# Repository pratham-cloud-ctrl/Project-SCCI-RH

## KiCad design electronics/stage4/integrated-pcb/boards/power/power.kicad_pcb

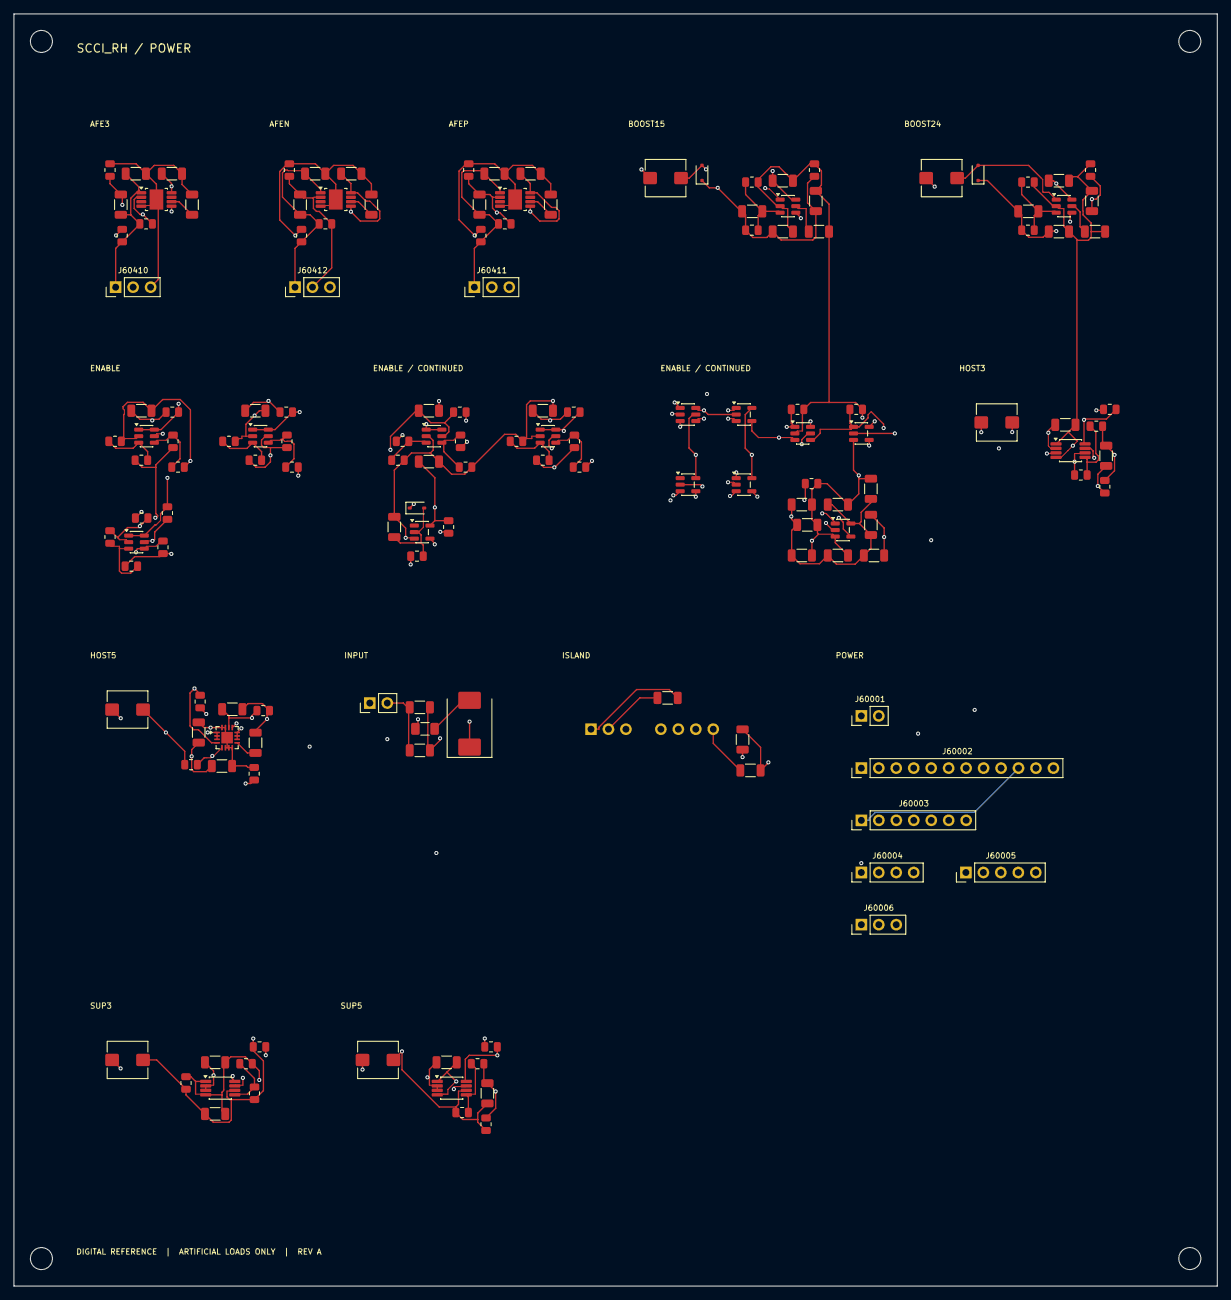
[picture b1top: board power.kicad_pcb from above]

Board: 4 copper layers, 175.0 x 185.0 mm, 160 parts (0 on the bottom side), 70 nets.

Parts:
C60001: 100u 16V LOW ESR; C_1206_3216Metric
C60002, C61102: 100n X7R 25V; C_1206_3216Metric
C60200, C60201, C60202, C60203, C60204, C60240, C60241, C60242, C60243, C60244, C60245, C60246, C60247: 100n X7R 16V; C_1206_3216Metric
C60230: 47n X7R 10%; C_1206_3216Metric
C60400, C61001, C61011, C61021, C61101: 22u X7R 16V; C_1206_3216Metric
C60401, C60402, C64100, C64110, C64120: 10u X7R 50V; C_1206_3216Metric
C61000, C61010, C61020, C61100, C63000, C63010: 10u X7R 25V; C_1206_3216Metric
C61103: 3.3n C0G 50V; C_1206_3216Metric
C63001, C63002, C63011, C63012: 22u X7R 50V; C_1206_3216Metric
C63003, C63013: 1u X7R 10V; C_1206_3216Metric
C63004, C63014: 4.7p C0G 50V; C_1206_3216Metric
C64101, C64111, C64121: 10u X7R 16V; C_1206_3216Metric
C64102, C64103, C64112, C64113, C64122, C64123: 10n C0G 50V; C_1206_3216Metric
D60001: SS34-E3/57T; D_SMC
D60230: BAT54WS-7-F; D_SOD-323
D60300, D60301: PMEG6010CEJ; D_SOD-323F
F60001: 2A FUSE 1206; Fuse_1206_3216Metric
H1, H2, H3, H4: MountingHole_3.2mm_M3
J60001: AT31004 PROTECTED 2S PACK / 6.4 TO 8.4V; PinHeader_1x02_P2.54mm_Vertical
J60002: POWER REQUEST / STATUS; PinHeader_1x12_P2.54mm_Vertical
J60003: HOST AND SUPERVISOR RAILS; PinHeader_1x07_P2.54mm_Vertical
J60004: FLOATING RECORDING RAILS; PinHeader_1x04_P2.54mm_Vertical
J60005: CONVERTER TEST POINTS; PinHeader_1x05_P2.54mm_Vertical
J60006: EXISTING MONITOR REFERENCES; PinHeader_1x03_P2.54mm_Vertical
J60410, J60411, J60412: QUIESCENT TRIM / TEST ONLY; PinHeader_1x03_P2.54mm_Vertical
L60100, L60101, L60102, L60110: 2.2uH SRP5030T-2R2M; L_Bourns_SRP5030T
L60300, L60301: 4.7uH SRP5030T-4R7M; L_Bourns_SRP5030T
R60230: 100k 1%; R_0805_2012Metric
R60231: 100R; R_0805_2012Metric
R60240, R60241, R60242, R62004, R62014, R62024, R62034, R62044: 10k; R_0805_2012Metric
R61000, R61020: 31250R 0.1%; R_0805_2012Metric
R61001, R61011, R61021: 10000R 0.1%; R_0805_2012Metric
R61002, R61012, R61022, R61102, R63002, R63012: 100k; R_0805_2012Metric
R61003, R61013, R61023, R61103, R64102, R64112, R64122: 47k; R_0805_2012Metric
R61010: 52500R 0.1%; R_0805_2012Metric
R61100: 52.5k 0.1%; R_0805_2012Metric
R61101, R62001, R62003, R62011, R62013, R62021, R62023, R62031, R62033, R62041, R62043, R64101, R64111, R64121: 10k 0.1%; R_0805_2012Metric
R62000: 155000R 0.1%; R_0805_2012Metric
R62002: 205000R 0.1%; R_0805_2012Metric
R62010: 67500R 0.1%; R_0805_2012Metric
R62012: 77500R 0.1%; R_0805_2012Metric
R62020: 108750R 0.1%; R_0805_2012Metric
R62022: 121250R 0.1%; R_0805_2012Metric
R62030: 89500R 0.1%; R_0805_2012Metric
R62032: 95500R 0.1%; R_0805_2012Metric
R62040: 39500R 0.1%; R_0805_2012Metric
R62042: 43000R 0.1%; R_0805_2012Metric
R63000: 418750R 0.1%; R_0805_2012Metric
R63001, R63011: 50k 0.1%; R_0805_2012Metric
R63010: 700000R 0.1%; R_0805_2012Metric
R64100: 19113.924R 0.1%; R_0805_2012Metric
R64110: 34725.738R 0.1%; R_0805_2012Metric
R64120: 33367.347R 0.1%; R_0805_2012Metric
SW60001: MASTER SPST / OFFBOARD; PinHeader_1x02_P2.54mm_Vertical
U60100, U60101, U60102: TPS62160DGKR; VSSOP-8_3x3mm_P0.65mm
U60110: TPS62130ARGTR; VQFN-16-1EP_3x3mm_P0.5mm_EP1.68x1.68mm
U60200, U60201, U60202, U60203, U60204: TPS3700DDCR; SOT-23-6
U60230: SN74LVC1G17DBVR; SOT-23-5
U60231, U60233: SN74LVC1G11DBVR; SOT-23-6
U60232, U60234, U60236, U60237: SN74LVC1G08DBVR; SOT-23-5
U60235: SN74LVC1G07DBVR; SOT-23-5
U60300, U60301: LT8330ES6#TRPBF; TSOT-23-6
U60400: TMR3-0522; TRACO_TMR3_SIP8_21.8x9.1_P2.54
U60410, U60411: TPS7A4901DGNR; Texas_DGN0008D_VSSOP-8-1EP_3x3mm_P0.65mm_EP2x2.94mm_Mask1.5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
U60412: TPS7A3001DGNR; Texas_DGN0008D_VSSOP-8-1EP_3x3mm_P0.65mm_EP2x2.94mm_Mask1.5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

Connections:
SYS_3fdd5066__AFE_P5: C64111.1, C64113.1, J60004.2, J60411.1, R64110.1, R64112.1, U60411.1
SYS_4f66f129__MON_VREF: J60006.1, R62030.1, R62032.1
SYS_37cfe02a__MON_VMID: J60006.2, R62040.1, R62042.1
SYS_65aafbb6__AFE_3V3: C64101.1, C64103.1, J60004.1, J60410.1, R64100.1, R64102.1, U60410.1
SYS_66aba95b__SUP_5: C61011.1, J60003.2, L60101.2, R61010.1, R61013.1, R62020.1, R62022.1, U60101.6
SYS_15689dc4__VH_24: C63011.1, C63012.1, C63014.1, D60301.1, J60003.6, R63010.1, R63012.1
SYS_56562df4__GND: C60001.2, C60002.2, C60200.2, C60201.2, C60202.2, C60203.2, C60204.2, C60230.2, C60240.2, C60241.2, C60242.2, C60243.2, C60244.2, C60245.2, C60246.2, C60247.2, C60400.2, C61000.2, C61001.2, C61010.2, C61011.2, C61020.2, C61021.2, C61100.2, C61101.2, C61102.2, C61103.2, C63000.2, C63001.2, C63002.2, C63003.2, C63010.2, C63011.2, C63012.2, C63013.2, J60001.2, J60002.12, J60003.7, J60005.5, J60006.3, R60240.2, R60241.2, R60242.2, R61001.2, R61003.2, R61011.2, R61013.2, R61021.2, R61023.2, R61101.2, R61103.2, R62001.2, R62003.2, R62011.2, R62013.2, R62021.2, R62023.2, R62031.2, R62033.2, R62041.2, R62043.2, R63001.2, R63002.2, R63011.2, R63012.2, U60100.1, U60100.4, U60101.1, U60101.4, U60102.1, U60102.4, U60110.6, U60110.7, U60110.8, U60110.15, U60110.16, U60110.17, U60200.2, U60201.2, U60202.2, U60203.2, U60204.2, U60230.3, U60231.2, U60232.3, U60233.2, U60234.3, U60235.3, U60236.3, U60237.3, U60300.2, U60301.2, U60400.1
SYS_08572049__HOST_3V3: C61021.1, J60003.3, L60102.2, R61020.1, R61023.1, U60102.6
SYS_ab932142__SUP_3V3: C60200.1, C60201.1, C60202.1, C60203.1, C60204.1, C60240.1, C60241.1, C60242.1, C60243.1, C60244.1, C60245.1, C60246.1, C60247.1, C61001.1, J60002.10, J60003.1, L60100.2, R60230.1, R60231.2, R61000.1, R61002.1, R61003.1, R61012.1, R61022.1, R61102.1, R62004.1, R62010.1, R62012.1, R62014.1, R62024.1, R62034.1, R62044.1, U60100.6, U60200.5, U60201.5, U60202.5, U60203.5, U60204.5, U60230.5, U60231.5, U60232.5, U60233.5, U60234.5, U60235.5, U60236.5, U60237.5
SYS_ce166826__HOST_5: C60400.1, C61101.1, J60003.4, L60110.2, R61100.1, R61103.1, U60110.14, U60400.2
SYS_d73cd2ee__AFE_N5: C64121.1, C64123.1, J60004.3, J60412.1, R64120.1, R64122.1, U60412.1
SYS_ee59c76b__PWR_FAULT_N: J60002.11, U60235.4
SYS_f199d834__PACK_BUS: C60001.1, C60002.1, C61000.1, C61010.1, C61020.1, C61100.1, C61102.1, C63000.1, C63010.1, J60005.1, L60300.1, L60301.1, SW60001.2, U60100.2, U60100.3, U60101.2, U60101.3, U60102.2, U60110.10, U60110.11, U60110.12, U60300.6, U60301.6
SYS_fb2237f8__VA_15: C63001.1, C63002.1, C63004.1, D60300.1, J60003.5, R63000.1, R63002.1
SYS_fca1c340__AFEAGND: C60401.2, C60402.2, C64100.2, C64101.2, C64102.2, C64110.2, C64111.2, C64112.2, C64120.2, C64121.2, C64122.2, J60004.4, J60005.4, J60410.3, J60411.3, J60412.3, R64101.2, R64102.2, R64111.2, R64112.2, R64121.2, R64122.2, U60400.7, U60410.4, U60410.9, U60411.4, U60411.9, U60412.4, U60412.9
power__AFE_3V3_FB: C64103.2, J60410.2, R64100.2, R64101.1, U60410.2
power__AFE_3V3_NR: C64102.1, U60410.6
power__AFE_N5_FB: C64123.2, J60412.2, R64120.2, R64121.1, U60412.2
power__AFE_N5_NR: C64122.1, U60412.6
power__AFE_P5_FB: C64113.2, J60411.2, R64110.2, R64111.1, U60411.2
power__AFE_P5_NR: C64112.1, U60411.6
power__BATT_OK: J60002.3, U60232.4, U60233.3
power__BATT_OV: R62002.2, R62003.1, U60200.4
power__BATT_UV: R62000.2, R62001.1, U60200.3
power__BATT_WINDOW_OK: R62004.2, U60200.1, U60200.6, U60232.1
power__BOOST_ENABLE: J60002.5, R60242.1, U60234.4, U60237.1, U60300.4, U60301.4
power__HOST_3V3_FB: R61020.2, R61021.1, U60102.5
power__HOST_3V3_PG: J60002.6, R61022.2, U60102.8
power__HOST_3V3_SW: L60102.1, U60102.7
power__HOST_5_FB: R61100.2, R61101.1, U60110.5
power__HOST_5_PG: J60002.7, R61102.2, U60110.4, U60234.2
power__HOST_5_SS: C61103.1, U60110.9
power__HOST_5_SW: L60110.1, U60110.1, U60110.2, U60110.3
power__HOST_15_FB: C63004.2, R63000.2, R63001.1, U60300.3
power__HOST_15_INTVCC: C63003.1, U60300.5
power__HOST_15_SW: D60300.2, L60300.2, U60300.1
power__HOST_ENABLE: J60002.4, R60241.1, U60102.3, U60110.13, U60233.4, U60234.1
power__ISO_N12: C60402.1, C64120.1, J60005.3, U60400.8, U60412.5, U60412.8
power__ISO_P12: C60401.1, C64100.1, C64110.1, J60005.2, U60400.6, U60410.5, U60410.8, U60411.5, U60411.8
power__MID_OV: R62042.2, R62043.1, U60204.4
power__MID_UV: R62040.2, R62041.1, U60204.3
power__MID_WINDOW_OK: R62044.2, U60204.1, U60204.6, U60236.2
power__MREF_OV: R62032.2, R62033.1, U60203.4
power__MREF_UV: R62030.2, R62031.1, U60203.3
power__MREF_WINDOW_OK: R62034.2, U60203.1, U60203.6, U60236.1
power__PACK_FUSED: D60001.2, F60001.2
power__PACK_POS: F60001.1, J60001.1, R62000.1, R62002.1
power__PACK_REVERSE_OK: D60001.1, SW60001.1
power__POWER_RUN_OK: U60235.2, U60237.4
power__PWR_REQUEST: J60002.1, R60240.1, U60233.1
power__PWR_START_DIS: D60230.1, R60231.1
power__PWR_START_OK: U60230.4, U60231.6, U60232.2
power__PWR_START_RC: C60230.1, D60230.2, R60230.2, U60230.2
power__REF_OK: U60236.4, U60237.2
power__S3_OV: R62012.2, R62013.1, U60201.4
power__S3_UV: R62010.2, R62011.1, U60201.3
power__S3_WINDOW_OK: R62014.2, U60201.1, U60201.6, U60231.1
power__S5_OV: R62022.2, R62023.1, U60202.4
power__S5_UV: R62020.2, R62021.1, U60202.3
power__S5_WINDOW_OK: R62024.2, U60202.1, U60202.6, U60231.3
power__SUP_3V3_FB: R61000.2, R61001.1, U60100.5
power__SUP_3V3_PG: J60002.8, R61002.2, U60100.8
power__SUP_3V3_SW: L60100.1, U60100.7
power__SUP_5_FB: R61010.2, R61011.1, U60101.5
power__SUP_5_PG: J60002.9, R61012.2, U60101.8
power__SUP_5_SW: L60101.1, U60101.7
power__SUP_READY: J60002.2, U60231.4, U60233.6
power__VH_24_FB: C63014.2, R63010.2, R63011.1, U60301.3
power__VH_24_INTVCC: C63013.1, U60301.5
power__VH_24_SW: D60301.2, L60301.2, U60301.1
